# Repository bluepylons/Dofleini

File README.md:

# Dofleini Controller

Dofleini is an STM32 controller with a USB-C connector, for the [Boston keyboard](https://github.com/bluepylons/Boston). The idea was to move all SMT components into a separate daughterboard. It can also theoretically be used on any keyboard with separated F-keys. It has a total of 29 I/O pins.

The electrical schematic is copied off of the Acheron [Austin](https://github.com/Gondolindrim/Austin). 

The headers are on a 2.54mm (0.1") grid.

## Copyright Notice

This project is released under the Acheron Open-Hardware License V1.1.

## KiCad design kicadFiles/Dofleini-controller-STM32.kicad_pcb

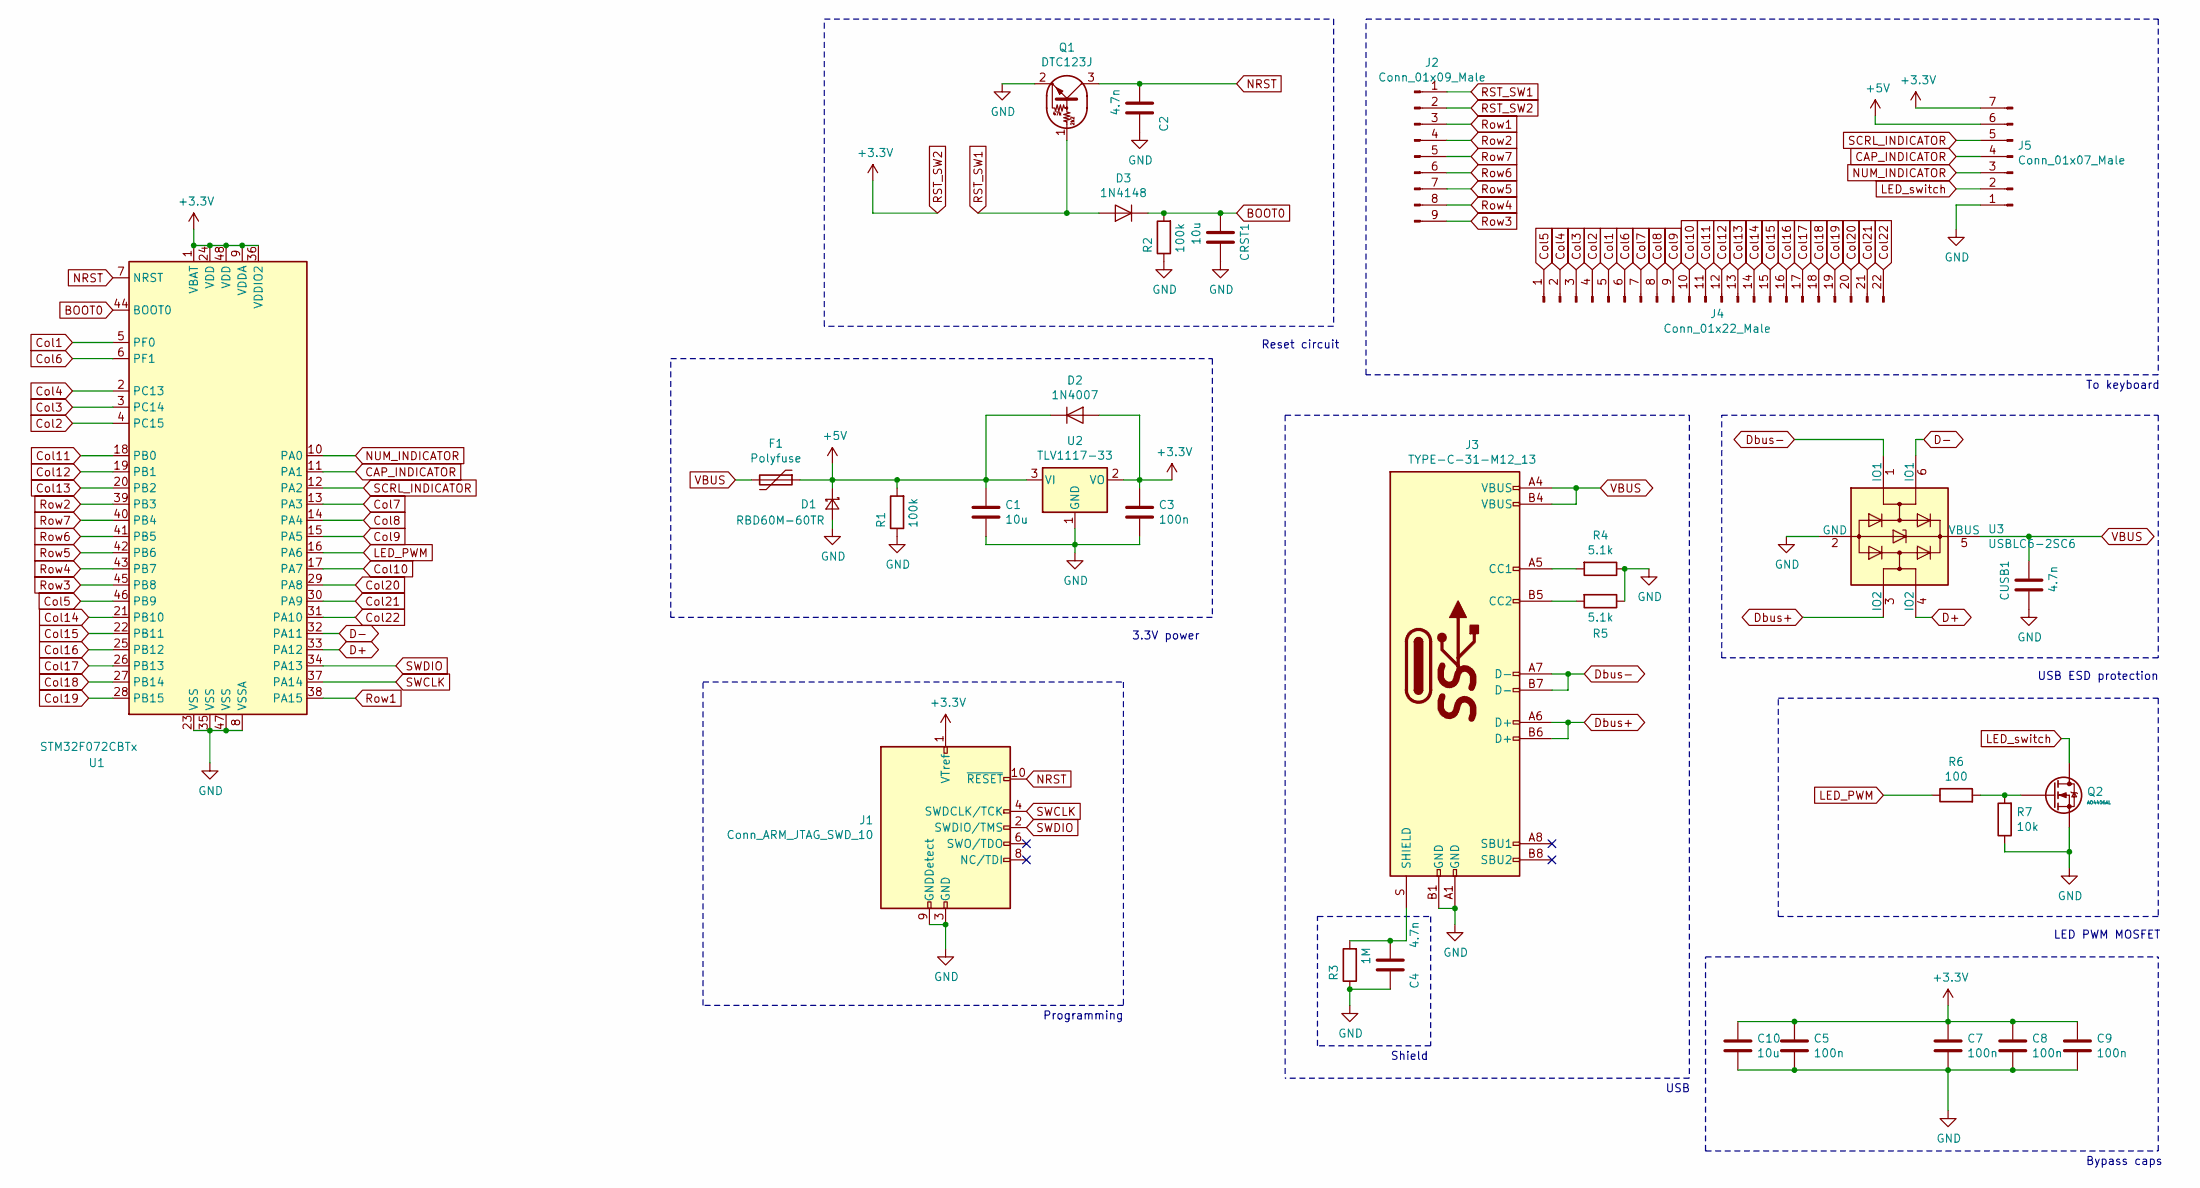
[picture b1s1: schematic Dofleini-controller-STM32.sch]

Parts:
C1, C10: 10u; C_0805_2012Metric_Pad1.15x1.40mm_HandSolder
C2, C4: 4.7n; C_0805_2012Metric_Pad1.15x1.40mm_HandSolder
C3, C5, C7, C8, C9: 100n; C_0805_2012Metric_Pad1.15x1.40mm_HandSolder
CRST1: 10u; C_0805_2012Metric_Pad1.15x1.40mm_HandSolder
CUSB1: 4.7n; C_0805_2012Metric_Pad1.15x1.40mm_HandSolder
D1: RBD60M-60TR; D_SOD-123
D2: 1N4007; D_DO-41_SOD81_P10.16mm_Horizontal
D3: 1N4148; D_DO-35_SOD27_P7.62mm_Horizontal
F1: Polyfuse; Fuse_1812_4532Metric_Pad1.30x3.40mm_HandSolder
J1: Conn_ARM_JTAG_SWD_10; PinHeader_1x10_P2.54mm_Vertical
J2: Conn_01x09_Male; PinHeader_1x09_P2.54mm_Vertical
J3: TYPE-C-31-M12_13; TYPE-C-31-M-12
J4: Conn_01x22_Male; PinHeader_1x22_P2.54mm_Vertical
J5: Conn_01x07_Male; PinHeader_1x07_P2.54mm_Vertical
Q1: DTC123J; SOT-23
Q2: AO4406AL; SOIC-8
R1, R2: 100k; R_0805_2012Metric_Pad1.15x1.40mm_HandSolder
R3: 1M; R_0805_2012Metric_Pad1.15x1.40mm_HandSolder
R4, R5: 5.1k; R_0805_2012Metric_Pad1.15x1.40mm_HandSolder
R6: 100; R_0805_2012Metric_Pad1.15x1.40mm_HandSolder
R7: 10k; R_0805_2012Metric_Pad1.15x1.40mm_HandSolder
U1: STM32F072CBTx; LQFP-48_7x7mm_P0.5mm
U2: TLV1117-33; SOT-223-3_TabPin2
U3: USBLC6-2SC6; SOT-23-6

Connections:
+5V: C1.1, D1.1 (K), D2.1 (K), F1.1, J5.6, R1.2, U2.3 (VI)
BOOT0: CRST1.1, D3.1 (K), R2.2, U1.44 (BOOT0)
CAP_INDICATOR: J5.4, U1.11 (PA1)
Col1: J4.5, U1.5 (PF0)
Col2: J4.4, U1.4 (PC15)
Col3: J4.3, U1.3 (PC14)
Col4: J4.2, U1.2 (PC13)
Col5: J4.1, U1.46 (PB9)
Col6: J4.6, U1.6 (PF1)
Col7: J4.7, U1.13 (PA3)
Col8: J4.8, U1.14 (PA4)
Col9: J4.9, U1.15 (PA5)
Col10: J4.10, U1.17 (PA7)
Col11: J4.11, U1.18 (PB0)
Col12: J4.12, U1.19 (PB1)
Col13: J4.13, U1.20 (PB2)
Col14: J4.14, U1.21 (PB10)
Col15: J4.15, U1.22 (PB11)
Col16: J4.16, U1.25 (PB12)
Col17: J4.17, U1.26 (PB13)
Col18: J4.18, U1.27 (PB14)
Col19: J4.19, U1.28 (PB15)
Col20: J4.20, U1.29 (PA8)
Col21: J4.21, U1.30 (PA9)
Col22: J4.22, U1.31 (PA10)
D+: U1.33 (PA12), U3.4 (IO2)
D-: U1.32 (PA11), U3.6 (IO1)
Dbus+: J3.A6 (D+), J3.B6 (D+), U3.3 (IO2)
Dbus-: J3.A7 (D-), J3.B7 (D-), U3.1 (IO1)
GND: C1.2, C2.2, C3.2, C4.2, C5.2, C7.2, C8.2, C9.2, C10.2, CRST1.2, CUSB1.2, D1.2 (A), J1.3 (GND), J1.5 (GND), J1.9 (GNDDetect), J3.A1 (GND), J3.B1 (GND), J5.1, Q1.2 (E), Q2.1, Q2.2, Q2.3, R1.1, R2.1, R3.1, R4.1, R5.1, R7.1, U1.8 (VSSA), U1.23 (VSS), U1.35 (VSS), U1.47 (VSS), U2.1 (GND), U3.2 (GND)
LED_PWM: R6.1, U1.16 (PA6)
LED_switch: J5.2, Q2.5 (D), Q2.6, Q2.7, Q2.8
NRST: C2.1, J1.10 (~RESET~), Q1.3 (C), U1.7 (NRST)
NUM_INDICATOR: J5.3, U1.10 (PA0)
unnamed: C4.1, J3.S (SHIELD), R3.2
unnamed: J3.A5 (CC1), R4.2
unnamed: J3.B5 (CC2), R5.2
unnamed: Q2.4 (G), R6.2, R7.2
RST_SW1: D3.2 (A), J2.1, Q1.1 (B)
RST_SW2: C3.1, C5.1, C7.1, C8.1, C9.1, C10.1, D2.2 (A), J1.1 (VTref), J2.2, J5.7, U1.1 (VBAT), U1.9 (VDDA), U1.24 (VDD), U1.36 (VDDIO2), U1.48 (VDD), U2.2 (VO)
Row1: J2.3, U1.38 (PA15)
Row2: J2.4, U1.39 (PB3)
Row3: J2.9, U1.45 (PB8)
Row4: J2.8, U1.43 (PB7)
Row5: J2.7, U1.42 (PB6)
Row6: J2.6, U1.41 (PB5)
Row7: J2.5, U1.40 (PB4)
SCRL_INDICATOR: J5.5, U1.12 (PA2)
SWCLK: J1.4 (SWDCLK/TCK), U1.37 (PA14)
SWDIO: J1.2 (SWDIO/TMS), U1.34 (PA13)
VBUS: CUSB1.1, F1.2, J3.A4 (VBUS), J3.B4 (VBUS), U3.5 (VBUS)

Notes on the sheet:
Shield
Bypass caps
USB ESD protection
USB
Reset circuit
3.3V power
To keyboard
LED PWM MOSFET
Programming

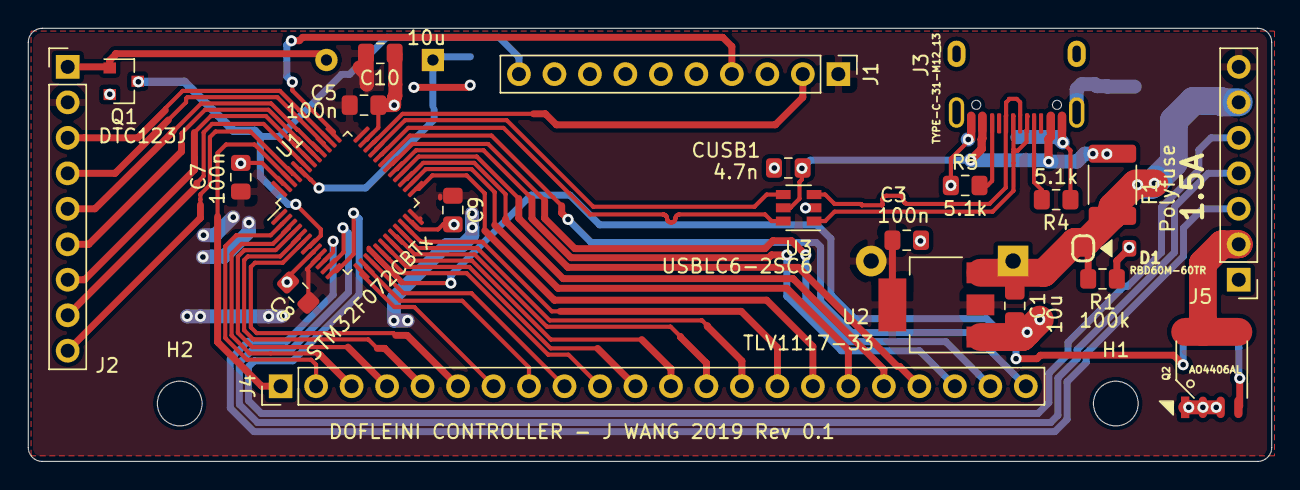
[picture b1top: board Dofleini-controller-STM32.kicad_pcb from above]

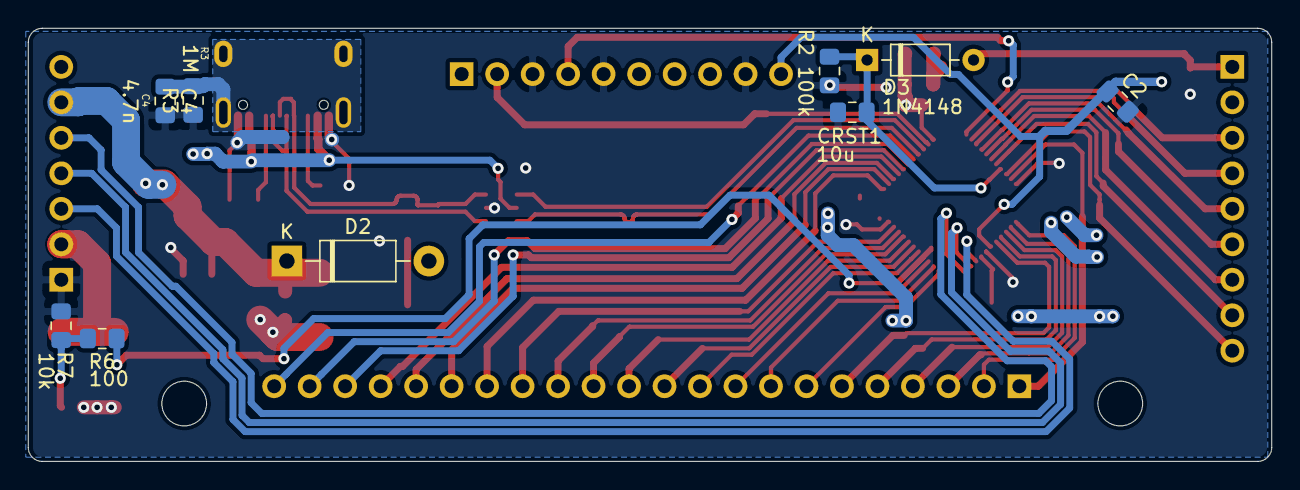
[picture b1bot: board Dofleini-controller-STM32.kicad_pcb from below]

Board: 2 copper layers, 89.0 x 31.0 mm, 34 parts (9 on the bottom side), 51 nets.

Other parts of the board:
H1, H2: MountingHole; MountingHole_3.2mm_M3_ISO7380

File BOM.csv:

,Value,,Part No,Mouser Link
">  C1, C10",10u,Capacitor_SMD:C_0805_2012Metric_Pad1.15x1.40mm_HandSolder,Taiyo Yuden LMK212ABJ106MG-T,https://www.mouser.com/ProductDetail/Taiyo-Yuden/LMK212ABJ10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 
">  C3, C5, C7-C9",100n,Capacitor_SMD:C_0805_2012Metric_Pad1.15x1.40mm_HandSolder,"Taiyo Yuden 
GMK212BJ104KGHT",https://www.mouser.com/ProductDetail/Taiyo-Yuden/GMK212BJ104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 
">  C2, C4",4.7n,Capacitor_SMD:C_0805_2012Metric_Pad1.15x1.40mm_HandSolder,Kemet C0805C472K5RACTU,https://www.mouser.com/ProductDetail/KEMET/C0805C472K5RACTU?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 
    CRST1,10u,Capacitor_SMD:C_0805_2012Metric_Pad1.15x1.40mm_HandSolder,Taiyo Yuden LMK212ABJ106MG-T,https://www.mouser.com/ProductDetail/Taiyo-Yuden/LMK212ABJ10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 
    CUSB1,4.7n,Capacitor_SMD:C_0805_2012Metric_Pad1.15x1.40mm_HandSolder,Kemet C0805C472K5RACTU,https://www.mouser.com/ProductDetail/KEMET/C0805C472K5RACTU?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 
    D1,RB060M-60TR,acheronComponents:D_SOD-123,RB060MM-60TFTR ,https://www.mouser.com/ProductDetail/ROHM-Semiconductor/RB06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 
    D2,1N4007,Diode_THT:D_DO-41_SOD81_P10.16mm_Horizontal,EIC 1N4007,https://www.taydaelectronics.com/1n4007-1a-1000v-rectifier-d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 
    D3,1N4148,Diode_THT:D_DO-35_SOD27_P7.62mm_Horizontal,,https://www.taydaelectronics.com/1n4148-switching-signal-diode.html 
    F1,Polyfuse,Fuse:Fuse_1812_4532Metric_Pad1.30x3.40mm_HandSolder,Littelfuse 1812L075PR,https://www.mouser.com/ProductDetail/Littelfuse/1812L075PR?q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 
">  H1, H2",MountingHole,MountingHole:MountingHole_3.2mm_M3_ISO7380,,
    J1,Conn_ARM_JTAG_SWD_10,Connector_PinHeader_2.54mm:PinHeader_1x10_P2.54mm_Vertical,,
    J2,Conn_01x09_Male,Connector_PinHeader_2.54mm:PinHeader_1x09_P2.54mm_Vertical,,
    J3,TYPE-C-31-M12_13,acheronConnectors:TYPE-C-31-M-12,HRO Type-C-31-M-12,https://lcsc.com/product-detail/USB-Connectors_Korean-Hropar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 
    J4,Conn_01x22_Male,Connector_PinHeader_2.54mm:PinHeader_1x22_P2.54mm_Vertical,,https://www.taydaelectronics.com/40-pin-2-54-mm-single-row-p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 
    J5,Conn_01x07_Male,Connector_PinHeader_2.54mm:PinHeader_1x07_P2.54mm_Vertical,,https://www.taydaelectronics.com/40-pin-2-54-mm-single-row-p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 
    Q1,DTC123J,Package_TO_SOT_SMD:SOT-23,Diodes Inc DDTC123JCA-7-F,https://www.mouser.com/ProductDetail/Diodes-Incorporated/DDT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 
    Q2,AO4406AL,acheronComponents:SOIC-8,,
">  R1, R2",100k,Resistor_SMD:R_0805_2012Metric_Pad1.15x1.40mm_HandSolder,Vishay CRCW0805100KJNEAC,
    R3,1M,Resistor_SMD:R_0805_2012Metric_Pad1.15x1.40mm_HandSolder,Vishay CRCW08051M00FKEAC,
">  R4, R5",5.1k,Resistor_SMD:R_0805_2012Metric_Pad1.15x1.40mm_HandSolder,Bourns CR0805-FX-5101ELF,
    R6,100,Resistor_SMD:R_0805_2012Metric_Pad1.15x1.40mm_HandSolder, Vishay CRCW0805100RFKEAC,
    R7,10k,Resistor_SMD:R_0805_2012Metric_Pad1.15x1.40mm_HandSolder,Vishay CRCW080510K0FKEAC,
    U1,STM32F072CBTx,Package_QFP:LQFP-48_7x7mm_P0.5mm,ST STM32F072CBT6,https://www.mouser.com/ProductDetail/511-STM32F072CBT6 
    U2,TLV1117-33,Package_TO_SOT_SMD:SOT-223-3_TabPin2,TI TLV1117-33IDCYR,
    U3,USBLC6-2SC6,Package_TO_SOT_SMD:SOT-23-6,USBLC6-2SC6Y ,https://www.mouser.com/ProductDetail/STMicroelectronics/USBL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

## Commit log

2020-02-23 Added mounting holes
2020-03-02 Added BOM
2020-03-06 Made BOM
